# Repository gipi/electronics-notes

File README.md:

Repository containing my notes about electronics.

You can read it at [Read the docs](http://electronics-notes.readthedocs.org/).

## Getting started

You need to install the dependencies

```
$ python3 -m pip install --user mkdocs python-markdown-math
```

and to read locally you need to do a simple

```
$ mkdocs serve
```

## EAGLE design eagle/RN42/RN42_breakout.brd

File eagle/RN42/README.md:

Simple breakout board to use with the RN42 bluetooth module.

This breakout exposes only the ``UART`` signals; can be used
with a voltage level different from the original 3.3V at which
is operating the RN42 module since this breakout contains a
voltage regulator and some components that do the conversion
for you from one logic level to another.

For more informations read the original [datasheet](0900766b811a8f51.pdf).

## Connect to

After a factory reset you need to enter (via ``UART``) the following

```
SA,0
R,1
```

otherwise it doesn't allow connection to it.

In order to find the address you can use ``hcitool`` and then connect

```
$ hcitool scan
Scanning ...
        00:06:66:7B:8B:4A       n/a
$ sudo rfcomm connect rfcomm0 00:06:66:7B:8B:4A
Connected /dev/rfcomm0 to 00:06:66:7B:8B:4A on channel 1
Press CTRL-C for hangup
```

From another terminal finally you can access the wireless ``UART``

```
$ sudo screen /dev/rfcomm0 115200 8N1
```

## Links

 - [wiki](https://eewiki.net/display/Wireless/Getting+Started+with+RN42+Bluetooth+Module)

## TODO

 - add tolerance values on the back
 - add pin for ``FACTORY_RESET`` or a button
 - add logic level shifter for ``CTS`` and ``RTS`` (**do not use them, the board is broken, you must solder the jumper SJ5**)
 - add programming-related pinout (see this [instructable](http://www.instructables.com/id/3-Bluetooth-HID-Module-HC05-With-RN42-Firmware/))

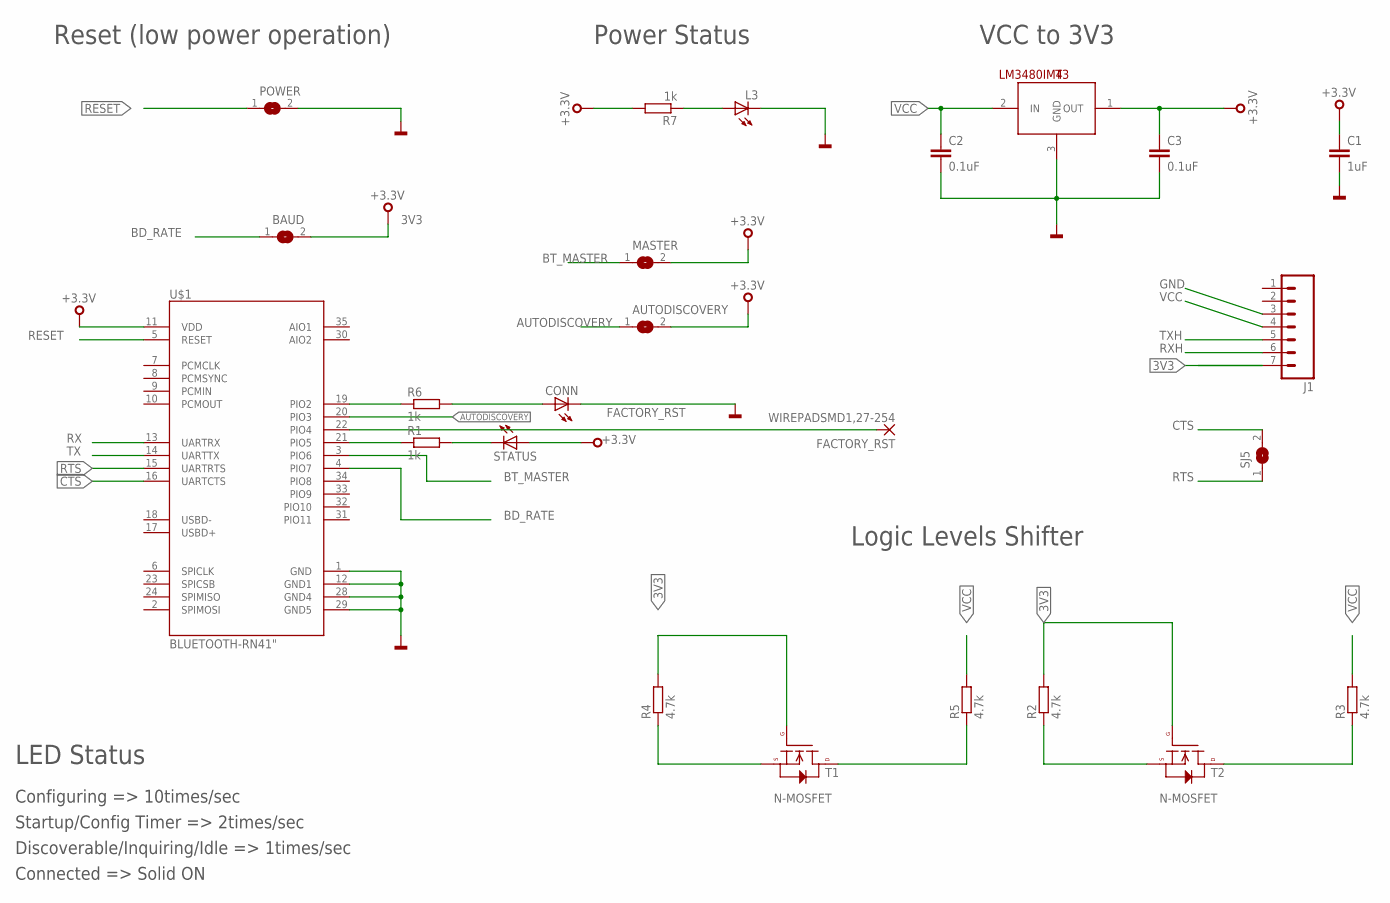
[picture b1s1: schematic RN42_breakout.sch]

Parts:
AUTODISCOVERY: SJ
BAUD: SJ
C1: 1uF; C0603
C2, C3: 0.1uF; 0603-CAP
CONN: LEDCHIPLED_0603; CHIPLED_0603
FACTORY_RST: WIREPADSMD1,27-254; SMD1,27-2,54
J1: M07; 1X07
L3: LEDCHIPLED_0603; CHIPLED_0603
MASTER: SJ
POWER: SJ
R1, R6, R7: 1k; R0603
R2, R3, R4, R5: 4.7k; R0603
SJ5: SJ
STATUS: LEDCHIPLED_0603; CHIPLED_0603
T1, T2: N-MOSFET; SOT23-3
T3: LM3480IM4; SOT23-3
U$1: BLUETOOTH-RN41"; RN41

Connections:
3V3: AUTODISCOVERY.2, BAUD.2, C1.1, C3.1, J1.7, MASTER.2, R2.2, R4.2, R7.2, STATUS.A, T1.1 (G), T2.1 (G), T3.1 (OUT), U$1.11 (VDD)
AUTODISCOVERY: AUTODISCOVERY.1, U$1.20 (PIO3)
BD_RATE: BAUD.1, U$1.4 (PIO7)
BT_MASTER: MASTER.1, U$1.3 (PIO6)
CTS: SJ5.2, U$1.16 (UARTCTS)
FACTORY_RST: FACTORY_RST.1, U$1.22 (PIO4)
GND: C1.2, C2.2, C3.2, CONN.C, J1.3, L3.C, POWER.2, T3.3 (GND), U$1.1 (GND), U$1.12 (GND1), U$1.28 (GND4), U$1.29 (GND5)
unnamed: R1.2, STATUS.C
unnamed: R1.1, U$1.21 (PIO5)
unnamed: CONN.A, R6.2
unnamed: L3.A, R7.1
RESET: POWER.1, U$1.5 (RESET)
RTS: SJ5.1, U$1.15 (UARTRTS)
RX: R2.1, T2.2 (S), U$1.13 (UARTRX)
RXH: J1.6, R3.1, T2.3 (D)
STATUS: R6.1, U$1.19 (PIO2)
TX: R4.1, T1.2 (S), U$1.14 (UARTTX)
TXH: J1.5, R5.1, T1.3 (D)
VCC: C2.1, J1.4, R3.2, R5.2, T3.2 (IN)

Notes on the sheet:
LED Status
Configuring => 10times/sec
Startup/Config Timer => 2times/sec
Discoverable/Inquiring/Idle => 1times/sec
Connected => Solid ON
Power Status
Reset (low power operation)
VCC to 3V3
Logic Levels Shifter

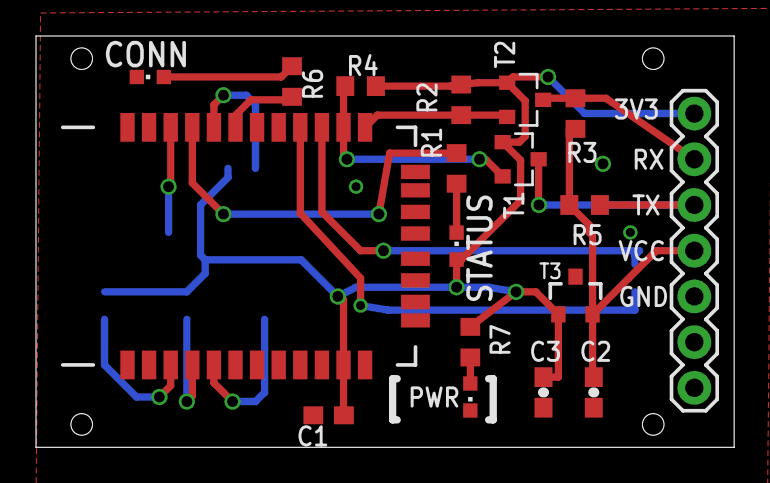
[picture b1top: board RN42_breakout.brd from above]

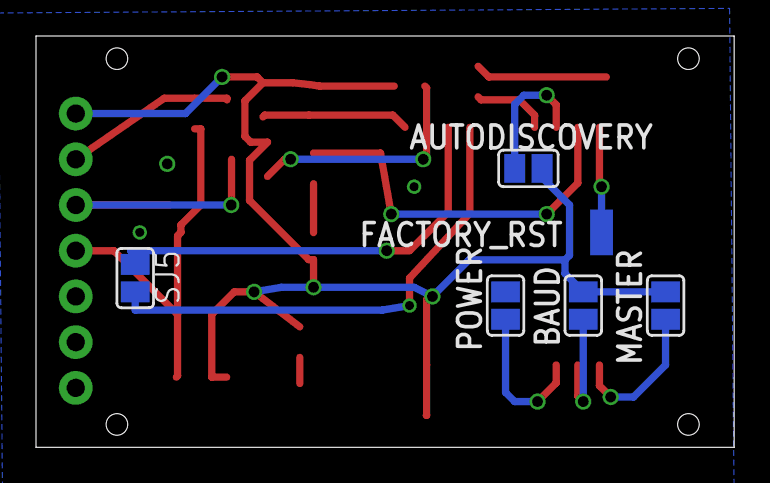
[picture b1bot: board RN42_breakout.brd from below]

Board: 2 copper layers, 38.8 x 22.9 mm, 24 parts (6 on the bottom side), 19 nets.

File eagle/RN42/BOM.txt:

Partlist exported from /opt/3043096/eagle/RN42/RN42_breakout.sch at 03/01/16 21:40

Part          Value              Device                  Package      Description                                   DATASHEET                                     DIGIKEY     ELEMENT14 OTHER URL                                                                                           
AUTODISCOVERY                    SJ                      SJ           SMD solder JUMPER                                                                                                                                                                                                     
BAUD                             SJ                      SJ           SMD solder JUMPER                                                                                                                                                                                                     
C1            1uF                C-EUC0603               C0603        CAPACITOR, European symbol                                                                                                                                                                                            
C2            0.1uF              CAP0603-CAP             0603-CAP     Capacitor                                                                                                                                                                                                             
C3            0.1uF              CAP0603-CAP             0603-CAP     Capacitor                                                                                                                                                                                                             
CONN                             LEDCHIPLED_0603         CHIPLED_0603 LED                                                                                                                                                                                                                   
FACTORY_RST   WIREPADSMD1,27-254 WIREPADSMD1,27-254      SMD1,27-2,54 Wire PAD connect wire on PCB                                                                                                                                                                                          
J1                               M07                     1X07         Header 7                                                                                                                                                                                                              
L3                               LEDCHIPLED_0603         CHIPLED_0603 LED                                                                                                                                                                                                                   
MASTER                           SJ                      SJ           SMD solder JUMPER                                                                                                                                                                                                     
POWER                            SJ                      SJ           SMD solder JUMPER                                                                                                                                                                                                     
R1            1k                 R-EU_R0603              R0603        RESISTOR, European symbol                                                                                                                                                                                             
R2            4.7k               R-EU_R0603              R0603        RESISTOR, European symbol                                                                                                                                                                                             
R3            4.7k               R-EU_R0603              R0603        RESISTOR, European symbol                                                                                                                                                                                             
R4            4.7k               R-EU_R0603              R0603        RESISTOR, European symbol                                                                                                                                                                                             
R5            4.7k               R-EU_R0603              R0603        RESISTOR, European symbol                                                                                                                                                                                             
R6            1k                 R-EU_R0603              R0603        RESISTOR, European symbol                                                                                                                                                                                             
R7            1k                 R-EU_R0603              R0603        RESISTOR, European symbol                                                                                                                                                                                             
SJ5                              SJ                      SJ           SMD solder JUMPER                                                                                                                                                                                                     
STATUS                           LEDCHIPLED_0603         CHIPLED_0603 LED                                                                                                                                                                                                                   
T1            N-MOSFET           NTR4501N   SOT23-3      N-Channel MOSFET Mode Field Effect Transistor
T2            N-MOSFET           NTR4501N   SOT23-3      N-Channel MOSFET Mode Field Effect Transistor
T3            LM3480IM4          LM3480IM4               SOT23-3      Small package linear regulator                                                                                                                                                                                        
U$1           BLUETOOTH-RN41"    BLUETOOTH-RN41"         RN41

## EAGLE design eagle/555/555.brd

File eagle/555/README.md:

# 555

Very simple implementation of the astable configuration
of a 555. In this directory are contained the schematics
and the layout.

## Layout

This is a layout developed with a protoboard in mind.

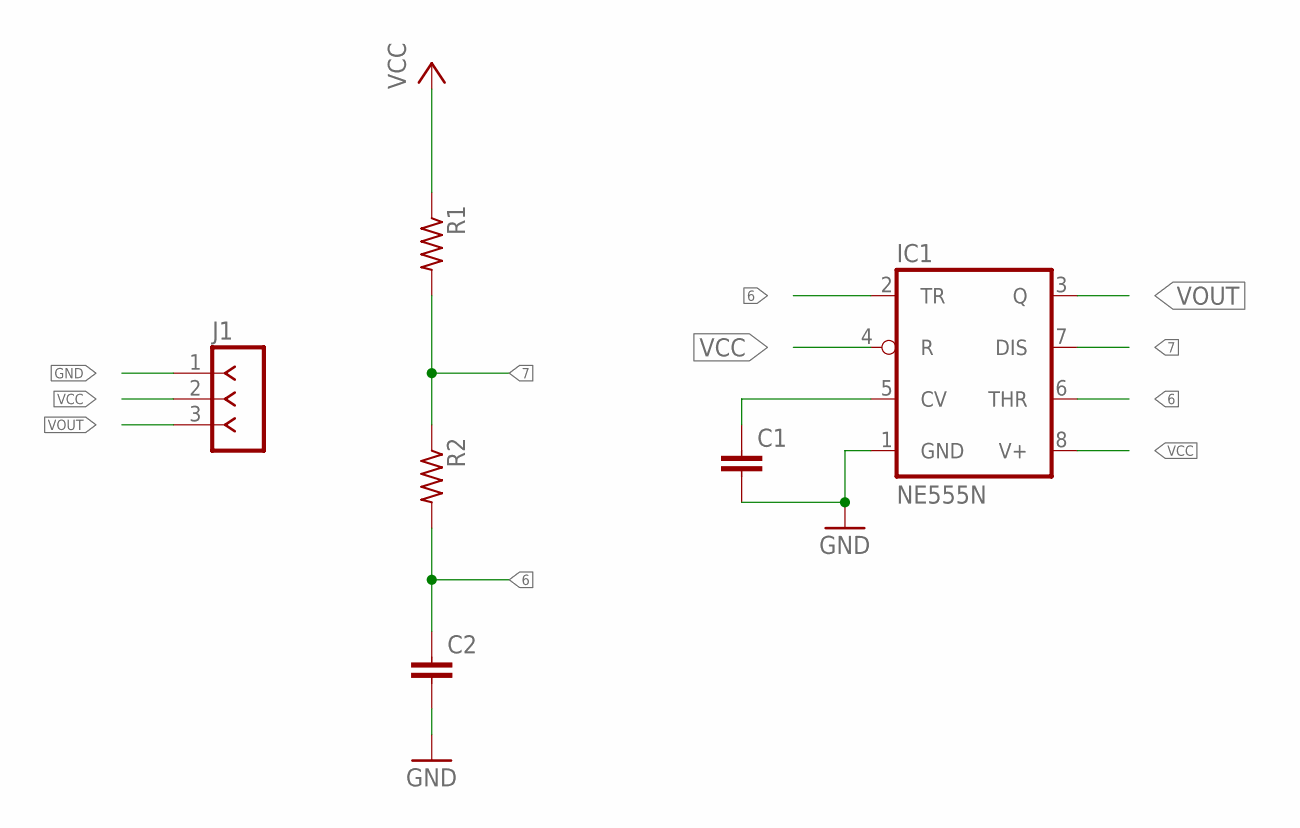
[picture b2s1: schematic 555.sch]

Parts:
C1, C2: C2.5/2; C2.5-2
IC1: NE555N; DIL08-ROUND
J1: F-1X03-SIP-100-40; SIP-100-03-40
R1, R2: R-US_0204/7; 0204/7

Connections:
6: C2.1, IC1.2 (TR), IC1.6 (THR), R2.2
7: IC1.7 (DIS), R1.2, R2.1
GND: C1.2, C2.2, IC1.1 (GND), J1.1
unnamed: C1.1, IC1.5 (CV)
VCC: IC1.4 (R), IC1.8 (V+), J1.2, R1.1
VOUT: IC1.3 (Q), J1.3

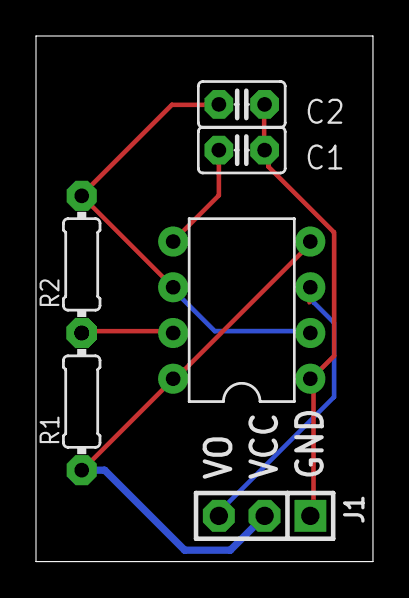
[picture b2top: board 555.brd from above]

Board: 2 copper layers, 18.7 x 29.2 mm, 6 parts (0 on the bottom side), 6 nets.

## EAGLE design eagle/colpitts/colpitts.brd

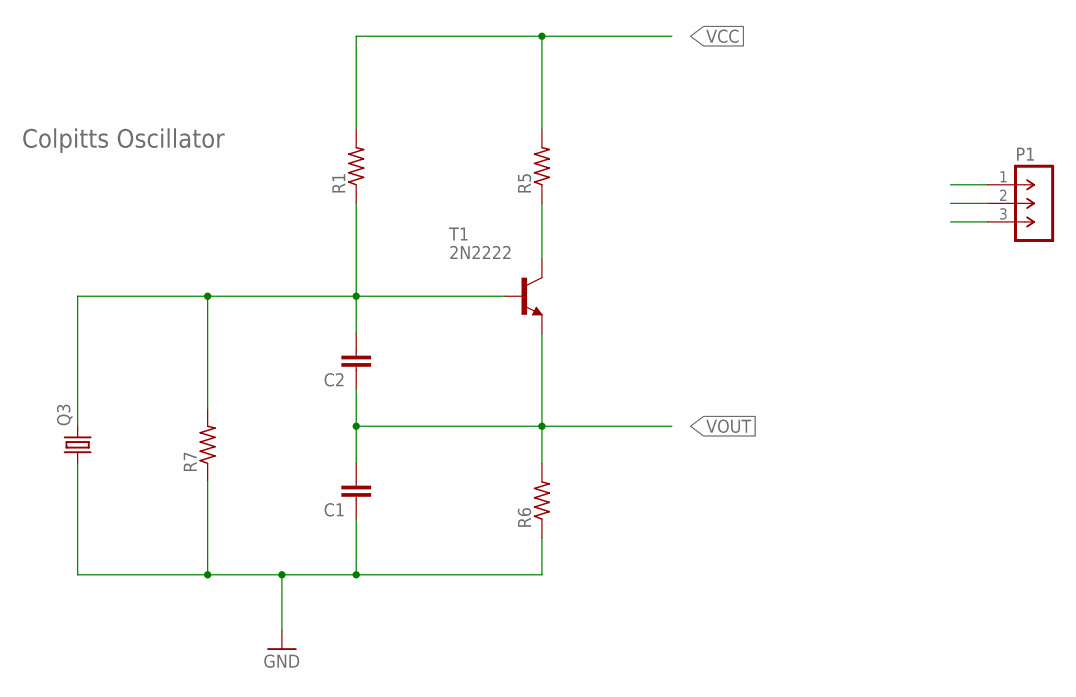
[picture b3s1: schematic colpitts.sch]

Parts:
C1, C2: C2,5-3; C2.5-3
P1: M-1X03-SIP-100-40; SIP-100-03-40
Q3: CRYSTALTC26V; TC26V
R1, R5, R6, R7: R-US_0204/5; 0204/5
T1: 2N2222; TO92-EBC-OVAL

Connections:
GND: C1.1, P1.3, Q3.1, R6.1, R7.1
unnamed: R5.1, T1.C
unnamed: C2.2, Q3.2, R1.1, R7.2, T1.B
VCC: P1.1, R1.2, R5.2
VOUT: C1.2, C2.1, P1.2, R6.2, T1.E

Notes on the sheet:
Colpitts Oscillator

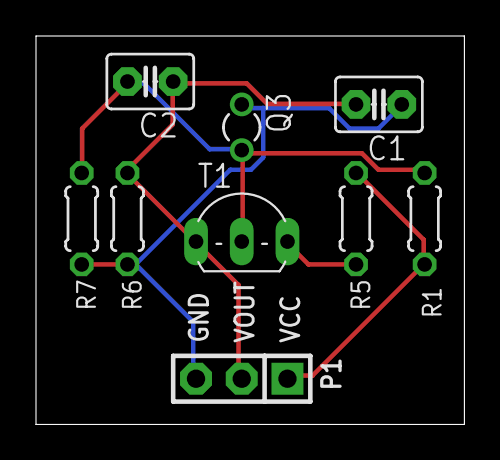
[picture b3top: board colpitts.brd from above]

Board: 2 copper layers, 23.8 x 21.6 mm, 9 parts (0 on the bottom side), 5 nets.

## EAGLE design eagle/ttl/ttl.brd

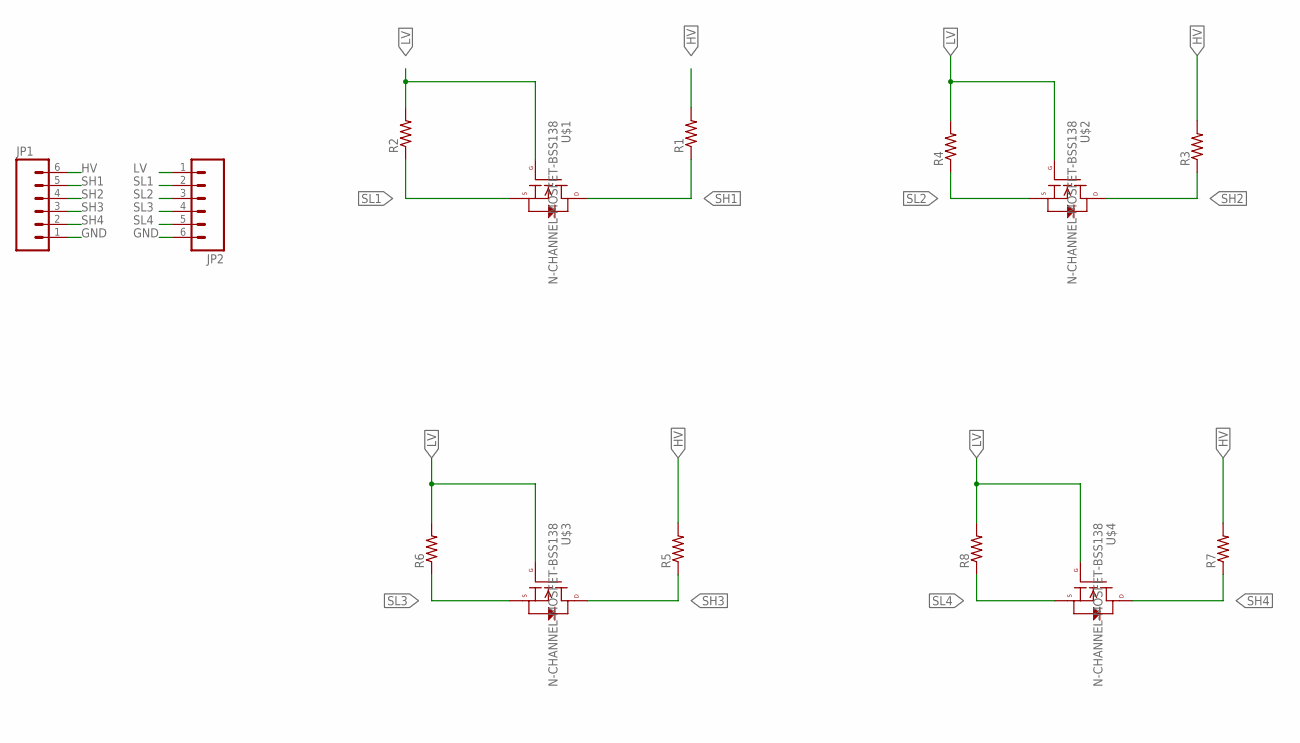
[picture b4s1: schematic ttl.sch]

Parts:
JP1, JP2: M06LOCK_LONGPADS; 1X06_LOCK_LONGPADS
R1, R2, R3, R4, R5, R6, R7, R8: RESISTOR0603-RES; 0603-RES
U$1, U$2, U$3, U$4: N-CHANNEL-MOSFET-BSS138; SOT23-3

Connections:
GND: JP1.1, JP2.6
HV: JP1.6, R1.2, R3.2, R5.2, R7.2
LV: JP2.1, R2.2, R4.2, R6.2, R8.2, U$1.1 (G), U$2.1 (G), U$3.1 (G), U$4.1 (G)
SH1: JP1.5, R1.1, U$1.3 (D)
SH2: JP1.4, R3.1, U$2.3 (D)
SH3: JP1.3, R5.1, U$3.3 (D)
SH4: JP1.2, R7.1, U$4.3 (D)
SL1: JP2.2, R2.1, U$1.2 (S)
SL2: JP2.3, R4.1, U$2.2 (S)
SL3: JP2.4, R6.1, U$3.2 (S)
SL4: JP2.5, R8.1, U$4.2 (S)

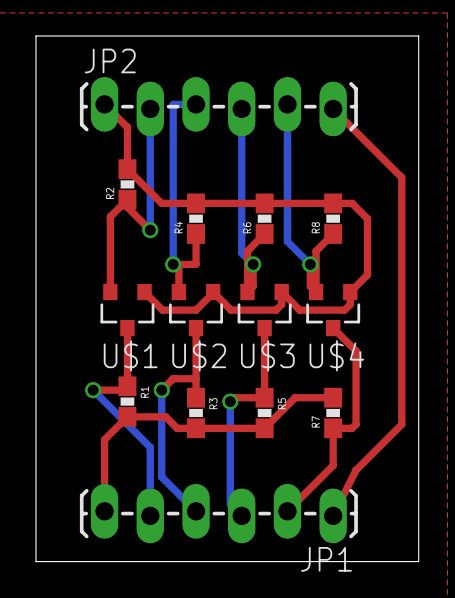
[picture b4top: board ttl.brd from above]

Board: 2 copper layers, 21.3 x 29.2 mm, 14 parts (0 on the bottom side), 11 nets.

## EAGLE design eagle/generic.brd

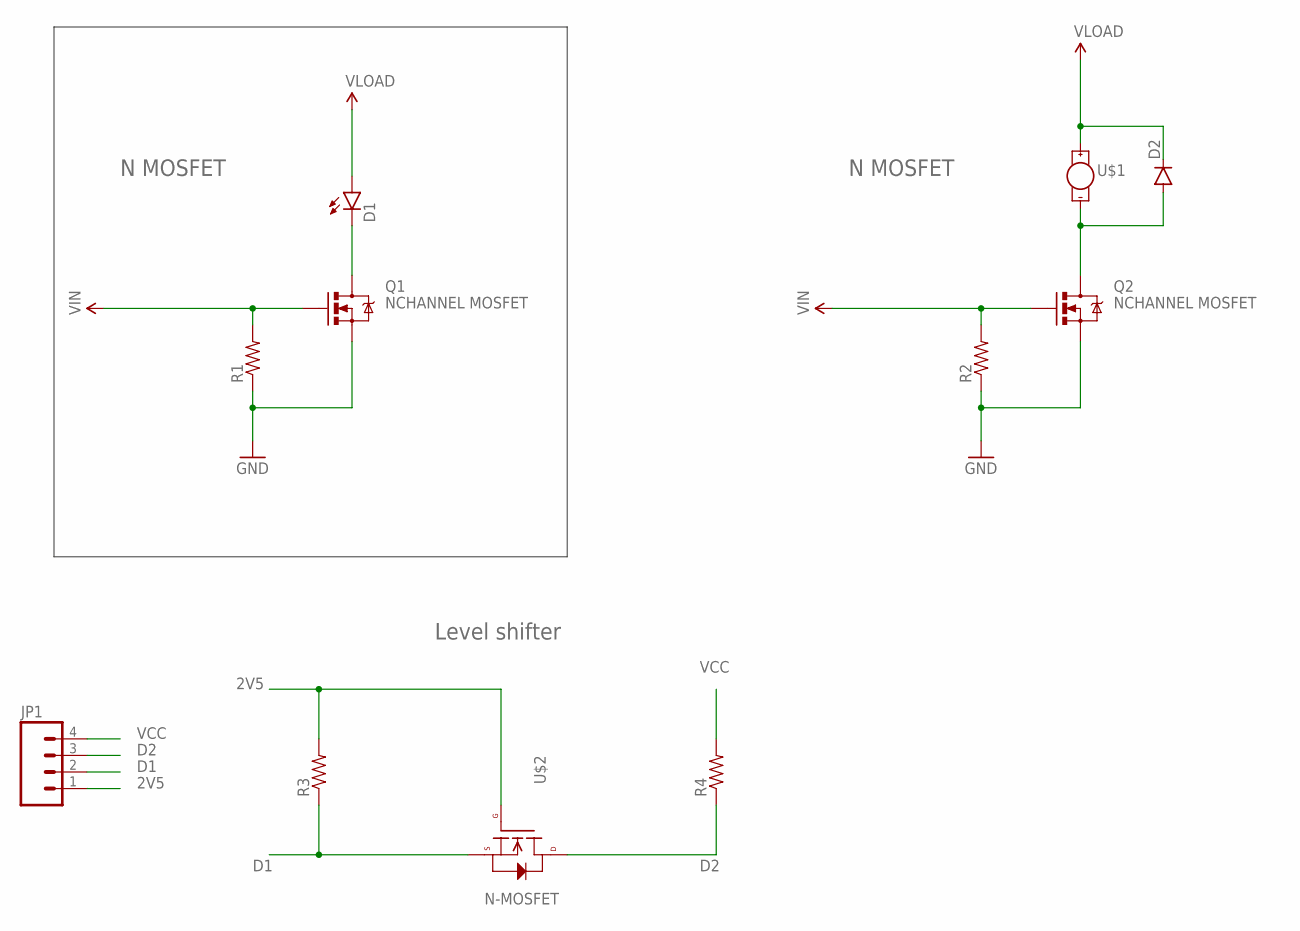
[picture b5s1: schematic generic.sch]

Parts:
D1: LED0603; LED-0603
D2: DIODESMB; SMB-DIODE
JP1: M04PTH; 1X04
Q1, Q2: NCHANNEL MOSFET; SOT323
R1, R2, R3, R4: RESISTOR0603-RES; 0603-RES
U$1: MOTOR10MM; VIBE-MOTOR-10MM
U$2: N-MOSFET; SOT23-3

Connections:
2V5: JP1.1, R3.2, U$2.1 (G)
5V: D1.A, D2.C
D1: JP1.2, R3.1, U$2.2 (S)
D2: JP1.3, R4.1, U$2.3 (D)
GND: Q1.2 (S), Q2.2 (S), R1.1, R2.1
unnamed: D2.A, Q2.3 (D)
unnamed: D1.C, Q1.3 (D)
VCC: JP1.4, R4.2
VIN: Q1.1 (G), Q2.1 (G), R1.2, R2.2

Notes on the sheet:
N MOSFET
Level shifter

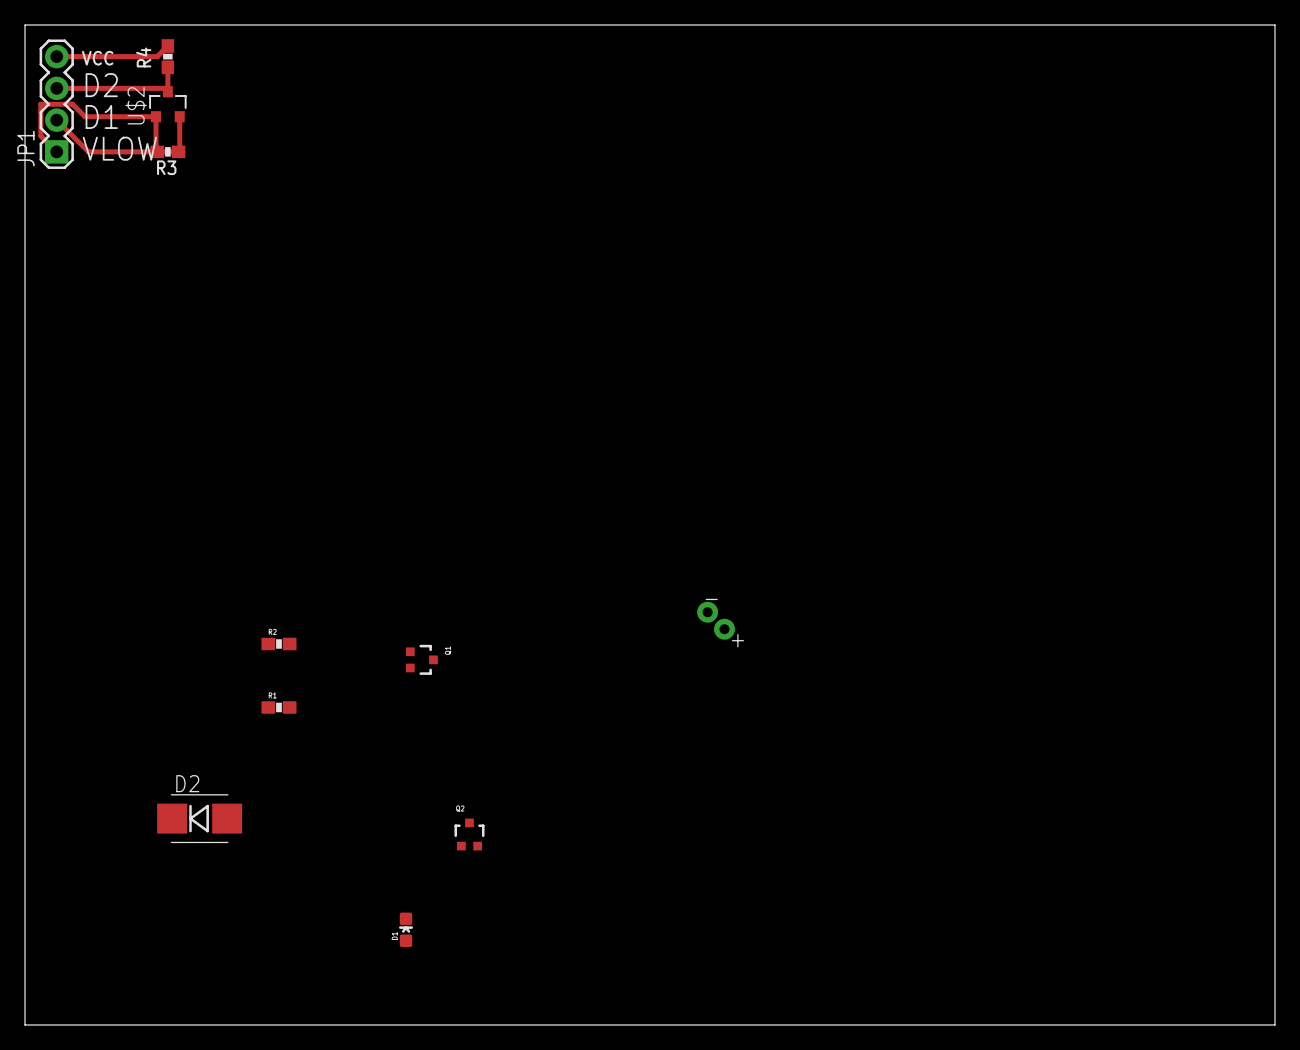
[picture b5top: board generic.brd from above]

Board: 2 copper layers, 100.0 x 80.0 mm, 11 parts (0 on the bottom side), 9 nets.

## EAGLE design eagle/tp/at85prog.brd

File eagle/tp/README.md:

# Tiny Programmer

Inspired by [this](https://www.tindie.com/products/bot_thoughts/eezee-tiny-breakout-programming-board-kit/) programmer layout at Tindie.com I worked on a similar
concept

It has a diode to protect programmer and power supply from each other current, has the
pin naming displayed and the header spacing allows to use in a breadboard (mounting
in the back side the header).

## TODO

 - Decoupling capacitor
 - power led indicator

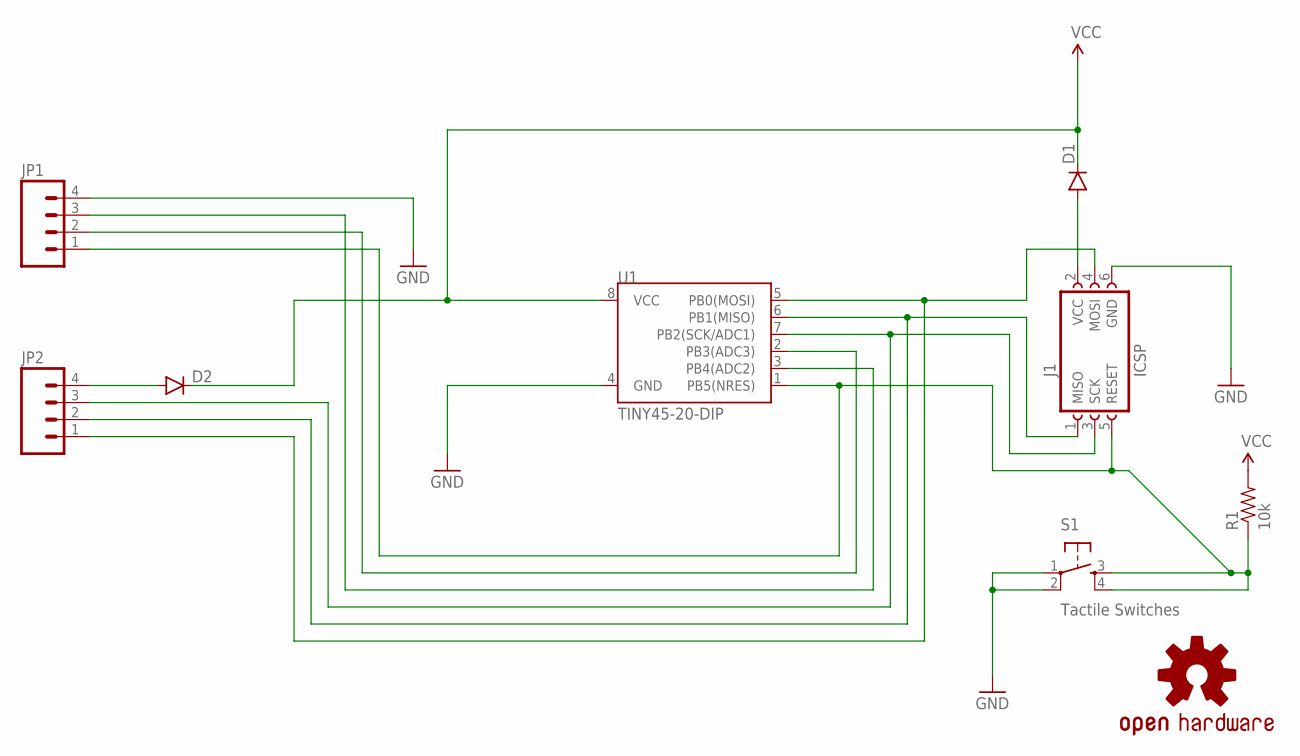
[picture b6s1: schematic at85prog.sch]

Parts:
D1, D2: DIODESMB; SMB-DIODE
J1: ICSP; 2X3
JP1, JP2: M04PTH; 1X04
LOGO1: OSHW-LOGOS; OSHW-LOGO-S
R1: 10k; 1206
S1: Tactile Switches; TACTILE-SWITCH-SMD
U1: TINY45-20-DIP; DIP08

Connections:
GND: J1.6 (GND), JP1.4, S1.1, S1.2
unnamed: J1.4 (MOSI), JP2.1, U1.5 (PB0(MOSI))
unnamed: J1.1 (MISO), JP2.2, U1.6 (PB1(MISO))
unnamed: J1.3 (SCK), JP2.3, U1.7 (PB2(SCK/ADC1))
unnamed: J1.5 (RESET), JP1.1, R1.1, S1.3, S1.4, U1.1 (PB5(NRES))
unnamed: JP1.2, U1.2 (PB3(ADC3))
unnamed: JP1.3, U1.3 (PB4(ADC2))
unnamed: D1.A, J1.2 (VCC)
unnamed: D2.A, JP2.4
VCC: D1.C, D2.C, R1.2, U1.8 (VCC)

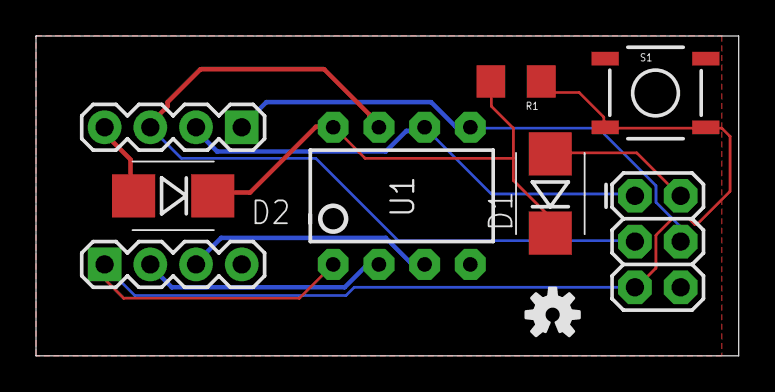
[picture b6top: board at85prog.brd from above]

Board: 2 copper layers, 39.0 x 17.8 mm, 9 parts (0 on the bottom side), 10 nets.

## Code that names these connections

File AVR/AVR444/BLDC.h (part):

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#define TRUE      (!FALSE)

//! Port pin connected to phase U, low side enable switch.
#define UL    PB5

//! Port pin connected to phase U, high side enable switch.
#define UH    PB4

//! Port pin connected to phase V, low side enable switch.
#define VL    PB3

//! Port pin connected to phase V, high side enable switch.
#define VH    PB2

//! Port pin connected to phase W, low side enable switch.
#define WL    PB1

//! Port pin connected to phase W, high side enable switch.
#define WH    PB0

//! Clockwise rotation flag. Used only in macros.
#define CW    0
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
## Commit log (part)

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2016-10-25 Add piece of code.
2016-10-26 fpga: counter increase with button pressing.
2016-12-02 Add links.
2016-12-13 Add note.
2016-12-30 Add Kicad links.
2017-01-10 Improve logic level notes.
2017-02-05 Improve KiCAD.
2017-02-05 Add an EasyDriver example sketch.
2017-02-12 Add opamp section.
2017-02-12 Add TODO.
2017-02-18 Add section about tape.
2017-02-18 Add note about enameled wire.
2017-02-20 Add 3D section.
2017-02-27 Add note about FDM.
2017-03-08 Add video.
2017-03-26 Try to use coregen.
2017-04-23 kicad: add simple audio amplifier circuit.
2017-05-08 Add Atmel's datasheets section.
2017-05-08 Add note about datasheet related infos.
2017-05-08 Fix link.
2017-05-15 Add example for setting fuse with avrdude.
2017-05-16 fpga: first module to dirty-glitching.
2017-05-19 fpga: very dirty code to glitch a clock.
2017-05-29 Fix.
2017-06-06 avr: add ISP pinout.
2017-06-06 laws: add note.
2017-06-06 RN42: improve info about default conf connection.
2017-06-07 RN42: add link to firmware stuff.
2017-06-30 RN42: update BOM.
2017-08-09 add SMA connectors information.
2017-12-06 VGA: add schematics.
2017-12-06 Add AVR444 application note code ported to avr-gcc.
2017-12-10 Add phase oscillator with kicad.
2017-12-10 Add page about simulation with spice.
2017-12-16 Dump some links.
2018-01-10 fpga: add PS2 simple controller.
    No error detection!
2018-01-10 fpga: add shift register verilog implementation.
2018-01-11 fpga/VGAGlyph: big rework.
2018-01-12 fpga/VGA: fix constraints file.
2018-01-12 fpga/VGAGlyph: fix reversed glyphs ROM and glyph_address.
2018-01-13 fpga/VGAGLyph: fix font rendering.
2018-01-13 fpga/VGAGlyph: add testbench for the framebuffer module.
    This testbench is probably bad written.
2018-02-19 Add script to read data from the SIGLENT SDS1102CML oscilloscope.
2018-02-20 test_visa: close device once.
2018-02-20 test_visa: display IDN for all the command involving the opened device.
2018-02-20 test_visa: add dumpscreen command.
2018-02-20 test_visa: add waveform dumping command.
2018-03-17 fpga: project GlitchGen.
2018-03-22 fpga/mojo/GlitchGen: add Arduino sketch.
2018-03-22 fpga/mojo/GlitchGen: refactor module for clock generation.
2018-04-11 GlitchGen: single stepping OK!
2018-04-11 GlitchGen: fix typo.
2018-04-11 GlitchGen: remove internal useless signal.
2018-04-11 GlitchGen: put the mojo clock into the clock network.
    In this way we can use it as a clock in the following modules.
2018-04-11 GlitchGen: make leds indicate some useful state.
2018-05-07 ESC: add simple code to use an ESC with arduino.
2018-05-10 PS/2: add working code.
2018-06-14 VGAGlyph: fix synch issue (?).
2018-06-14 VGAGlyph: use the same clock for h/vsync and framebuffer.
2018-06-14 Add reset input to VGA module.
2018-06-16 Change default net type to none.
2018-06-16 Let inDisplayArea be in sync with CounterX and CounterY.
2018-06-16 Delay also inDisplayArea.
2018-06-16 Improve comment.
2018-07-16 kicad: add mojo shield.
    It contains SDRAM, Flash, VGA and PS2.
2018-08-19 Fix AMS1117 pad net.
    In the original datasheet is not indicated that the bigger pad is vout
    and not ground how any sensible human could think.
2018-08-27 Fix the read the docs configuration file.
2018-09-08 fpga: fix UCF for SDRAM.
2018-09-08 fpga: rename variable.
2018-09-08 kicad: improve info about memories board.
2018-09-12 kicad: mojo header PS/2 holes enlargement.
2018-09-13 kicad: enlarged footprint for capacitor 0402 for hand soldering.
2018-09-24 kicad: fix name for mojo header pins.
2018-09-24 kicad/memories/pcb: fix R-2R ladder labels.
2018-10-03 fpga/VGA: upgrade controller to use 9-bit color depth.
2018-12-04 AVR/KeyboardMatrixRecovery: add POC.
2018-12-07 KeyboardMatrixRecovery: improve matrix recovery sketch.
    Now print only a key the moment when is pressed and output a binary packet.
2018-12-08 RN42: add datasheet.
2018-12-09 AVR/KeyboardMatrixRecovery: update README.
2018-12-28 Fix markdown extension error.
    <Config value: 'markdown_extensions'. Error: Failed to initiate extension 'math': 'module' object has no attribute 'makeExtension'>
    probably the naming convention is changed and had to be fixed, see
    <https://python-markdown.github.io/change_log/release-2.5/>.
2019-02-03 VGASOC: add ring_counter module and verilator POC.
2019-03-31 kicad: add samsung-jig.
2019-03-31 kicad: semi-final version of galaxy-jig.
2019-04-07 Add diagram of the JTAG stack.
2019-04-07 Fix typo.
2019-05-19 kicad/galaxy-jig: add notes.
2020-05-12 fpga/VGAGlyph: implement block ram and its simulation.
2020-05-12 fgpa/VGAGlyph: reimplement block rom for the glyph with simulation.
    Launch sim/obj_dir/Vglyph_rom and see the output of the block rom.
2020-05-12 fpga: add reset signal to hvsync_generator.
2020-05-12 fpga/VGAGlyph: rework verilog so to have simulation.
    $ cd fpga/mojo/VGAGlyph/sim
    $ make vga && ./obj_dir/VVGA
    ...
    [+] starting VGA simulation
    [-> dumping frame frames/frame-00000000.bmp at idx 6]
    [-> dumping frame frames/frame-00000001.bmp at idx 1182312]
2020-05-14 fpga/VGASOC: start implementing CPU.
2020-05-17 fpga/VGASOC: first implementation of the load instruction assembly.
2020-05-17 Add some links and notes.
2020-05-17 fpga/VGAGlyph: add clean target.
2020-05-17 fpga/VGASOC: add note about flags.
2020-05-17 fpga/VGASOC: fix compilation warning.
2020-05-18 fpga/VGASOC: remove MOVE instruction.
    Can be implemented with "ld rd, rs".
2020-05-21 fpga/VGASOC: factorize code about pipeline and add tests.
2020-05-21 Fix bug on parsing left operand.
2020-05-21 fpga/VGASOC: rework a little LOAD instruction assembly.
2020-05-21 fpga/VGASOC: start to implement JUMP instruction.
2020-05-23 fpga/VGASOC: improve Instruction{,Impl} classes.
2020-05-23 fpga/VGASOC: improve jump instruction.
    Now save the return address.
2020-05-23 fpga/VGASOC: start implementing the flags register.
2020-05-23 fpga/VGASOC: start implementing add instruction.
2020-05-23 fpga/VGASOC: improve operand parsing.
2020-05-23 Cleaning.
2020-05-26 fpga/VGASOC: add fetch module.
2020-05-26 Ignore obj_dir/
2020-05-27 fpga/VGASOC: improve fetch module.
2020-05-31 fpga/VGASOC: reworking decode and execute modules.
2020-05-31 fgpga/VGASOC: give a default (void) implementation for validate() and parseOpcode().
2020-06-02 fpga/VGASOC: start to organize the internal memory.
2020-06-02 fpga/VGASOC: change bootrom code (now with relative jumps!).
2020-06-02 fpga/VGASOC: implement relative jump.
2020-06-02 fpga/VGASOC: improve assembler output.
2020-06-02 fpga/VGASOC: bootrom -> wb_memory.
    Change the name to reflect the generic use.
2020-06-03 fpga/VGASOC: implement multiplication.
2020-06-03 fpga/VGASOC: use some parameters.
2020-06-03 fpga/VGASOC: set next program counter at the decode phase.
    So we don't have a race condition with the jump instruction.
2020-06-03 fpga/VGASOC: improve boolean condition.
2020-06-06 fpga/SOC: rename project.
2020-06-06 fpga/SOC: start to implement the memory stage.
2020-06-06 fpga/SOC: start implementing push instruction.
    Now we are writing to memory, we modified the fetch module as a general
    purpose master wishbone controller (a lot remains to do to have something
    not so shitty).
2020-06-06 fpga/SOC: rework enable_fetch.
    The enable signal for the wishbone master must be "one-shot", I'm not sure
    how good this strategy is.
2020-06-06 fpga/SOC: hardfix the simulation logging.
2020-06-06 fpga/SOC: add comments and .word directive.
2020-06-07 fpga/SOC: fix(?) write enable signal for the fetch module.
2020-06-07 fpga/SOC: add subroutine to the bootrom.
2020-06-08 fpga/SOC: start implementing pop instruction.
    FIXME: the input line for the memory is not driven so the push itself
    is not working.
2020-06-08 fpga/SOC: handle empty lines in the assembler.
2020-06-14 fpga/SOC: rework assembler to handle labels.
    Logging added with plog.
2020-06-14 fpga/SOC: fix internal SRAM size.
2020-06-14 fpga/SOC: update README.
2020-06-20 fpga/SOC: refactor code:
    Separate ISA from simulation and create distinct Makefiles.
2020-06-20 fpga/SOC: fix i_addr signal width.
2020-06-21 fpga/SOC: use stderr for logging.
2020-06-21 fpga/SOC: refactor bootrom code into its own directory.
2020-06-21 fpga/SOC: improve ISA documentation with opcode list.
2020-06-21 fpga/SOC: improve "unit testing" for instructions.
2020-06-21 fpga/SOC: fix directive encoding.
2020-06-24 fpga/SOC: fix jump instruction test.
2020-06-24 fpga/SOC: use the actual address contained in PC, not the incremented one.
2020-06-24 fpga/ROM: remove code I don't remember anymore.
2020-07-05 fpga/SOC: a little rework of Makefiles.
2020-07-05 fpga/SOC: use localparam.
2020-07-05 fpga/SOC: de-assert o_done when starting transmissions.
2020-07-05 fpga/SOC: add primitive wishbone controller for UART.
2020-07-06 fpga/SOC: improve and add test for wb_uart.
2020-07-12 fpga/SOC: rework flags handling.
2020-07-12 fpga/SOC: rework cpusim to use SysCon class.
2020-07-12 fpga/SOC: handle memory transaction during instructions tests.
2020-07-12 fpga/SOC: import gtkwave predefined signals "save file".
2020-07-13 fpga/SOC: don't use hex for registers index.
2020-07-13 fpga/SOC: add tests for pop/push instructions.
2020-07-14 fpga/SOC: implement store instruction.
2020-07-14 fpga/SOC: add check for wishbone write enable signal during tests.
2020-07-18 fpga/SOC: port soc.cpp to use peripherals templates.
2020-07-18 Fix uart
2020-07-18 Improve README.
2020-07-19 fpga/SOC: add baudgenerator module.
    For now is only simulated with clk generated equals to the main one.
2020-07-19 fpga/SOC: rework memory accesses to allow variable sizes.
    Now it's possible to have byte/short/word sized accesses.
2020-07-19 fpga/SOC: start to implement variable encoding assembler output.
2020-07-19 fpga/SOC: save gtkwave signal configuration for the SoC.
2020-07-26 fpga/SOC: remove traces when cleaning.
2020-07-26 fpga/SOC: make the bootrom path absolute.
2020-08-08 Fix counter wrong size.
    Thank to @MuhammadAlBarham for spotting the error. This fixes #1 .
2020-12-17 fpga/SOC/asm: add check for the right operand of a LD instruction.
2020-12-17 fpga/SOC: improve simulation for glyph ROM.
2020-12-17 fpga/SOC: add new test case.
2020-12-17 fpga/SOC: add header file dependencies for asm.
2020-12-17 fpga/SOC: add note about 4 bytes aligning for PC and SP.
2020-12-17 fpga/SOC: rework wishbone bus.
2020-12-18 fpga/SOC: make ACK for slave HiZ when not selected.
2020-12-18 fpga/SOC: rework tick().
2020-12-18 fpga/SOC: use enum for opcodes.
2020-12-18 fpga/SOC: fix slave selection logic.
2020-12-18 fpga/SOC: add jump relative test.
2020-12-18 fpga/SOC: improve logging on cpu simulation.
    Add description of the specific tests.
2021-03-24 Add note about solder wick.
2021-03-24 Update pinout image.
2021-04-17 Add requirements file.
2021-04-17 Fix image path.
2021-04-17 Add readthedocs configuration file.
2021-04-17 Add Arduino Mega pinout.
2021-04-22 Fix AVR makefile.
2021-04-22 Add code for ecg.
2021-04-22 AVR/ECG: reformat code for USB_COM_vect.
2021-04-22 AVR/ECG: fix wrong register for DETACH.
2021-04-22 AVR/ECG: add ADC routines.
2021-04-23 AVR/ECG: configure for the AD8232 board.
2021-04-23 AVR/ECG: fix declaration.
2021-04-23 AVR/sd-reader: import project from www.roland-riegel.de/sd-reader/.
2021-04-23 AVR/SD-READER: adapt code for atmega32u4.
2021-04-25 AVR/blink: add simple project to blink a led.
2021-04-29 STM32: add PoC blink baremetal.
2021-05-04 Fix SD Card related links.
2021-06-18 Fix micro pinout.
2021-06-24 AVR/KeyboardMatrixRecovery: add script to generate layout.
2021-10-20 Add some links.
2021-11-27 Add note about leds orientation.
2021-11-27 Add note about capacitor applications.
2021-12-05 Update mkdocs version.
2022-04-03 Add some notes
2022-04-03 Update dependencies.

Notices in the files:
parts and their libraries:
con-headers-jp: Copyright (C) 2008, Bob Starr
SparkFun-Connectors: Licensing: Creative Commons ShareAlike 4.0 International - https://creativecommons.org/licenses/by-sa/4.0
